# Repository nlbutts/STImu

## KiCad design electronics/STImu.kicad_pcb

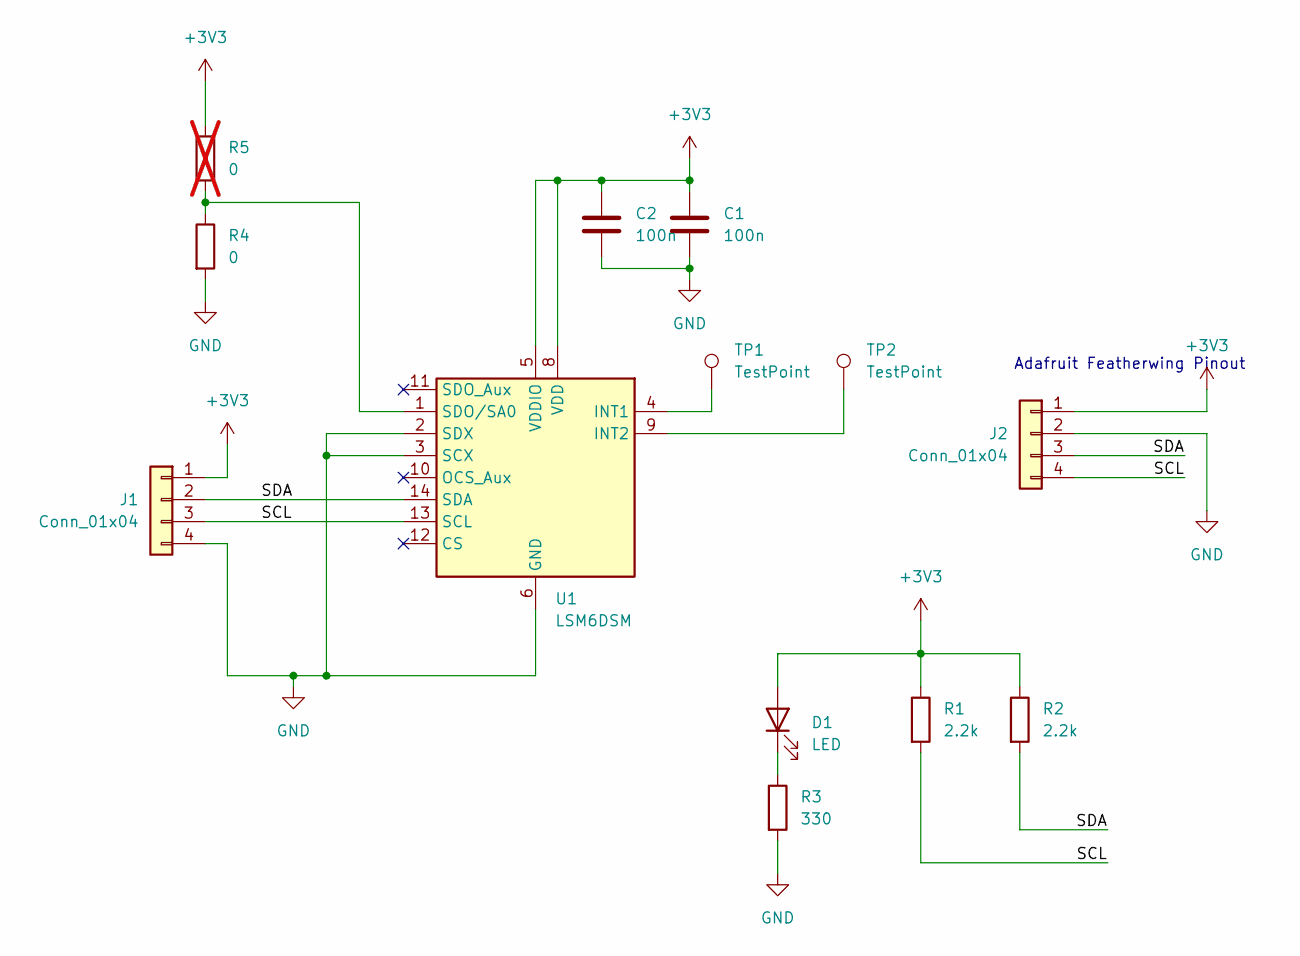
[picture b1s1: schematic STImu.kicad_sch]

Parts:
C1, C2: 100n; C_0603_1608Metric
D1: LED; LED_0603_1608Metric
J1, J2: Conn_01x04; FanPinHeader_1x04_P2.54mm_Vertical
R1: 2.2k; LED_0603_1608Metric
R2: 2.2k; R_0603_1608Metric
R3: 330; R_0603_1608Metric
R4: 0; LED_0603_1608Metric
R5: 0; LED_0603_1608Metric; not fitted
TP1, TP2: TestPoint; TestPoint_Pad_D1.0mm
U1: LSM6DSM; LGA-14_3x2.5mm_P0.5mm_LayoutBorder3x4y

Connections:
+3V3: C1.1, C2.1, D1.2 (A), J1.1, J2.1, R1.1, R2.1, R5.1, U1.5 (VDDIO), U1.8 (VDD)
/SCL: J1.3, J2.4, R1.2, U1.13 (SCL)
/SDA: J1.2, J2.3, R2.2, U1.14 (SDA)
GND: C1.2, C2.2, J1.4, J2.2, R3.2, R4.2, U1.2 (SDX), U1.3 (SCX), U1.6 (GND), U1.7 (GND)
unnamed: D1.1 (K), R3.1
unnamed: TP1.1, U1.4 (INT1)
unnamed: TP2.1, U1.9 (INT2)
unnamed: R4.1, R5.2, U1.1 (SDO/SA0)

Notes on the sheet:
Adafruit Featherwing Pinout

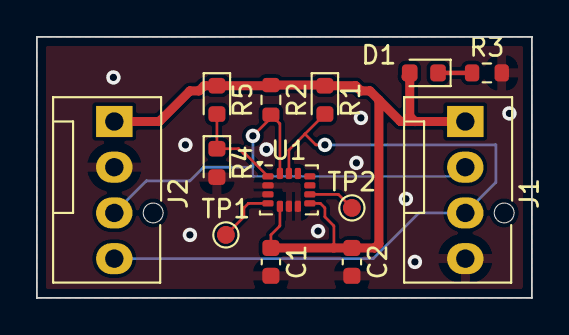
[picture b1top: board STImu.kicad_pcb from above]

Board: 2 copper layers, 27.5 x 14.5 mm, 13 parts (0 on the bottom side), 8 nets.

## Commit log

2024-08-02 Initial checkin.
2024-08-15 This is what was actually ordered.

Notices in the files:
electronics/STImu.kicad_pcb:
Copyright 2024
